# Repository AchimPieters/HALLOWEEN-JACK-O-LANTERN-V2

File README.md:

# HALLOWEEN-JACK-O-LANTERN-V2
 Halloween – Jack O’ Lantern V2: Ultimate Fire Effect

This project is a next-level version of the original [Jack O’ Lantern](#) flickering flame. It uses an ATtiny85 and six individually controlled LEDs to simulate a more realistic and dynamic fire effect — perfect for Halloween decorations, cosplay props, fantasy builds, and magical scenes.

Now with optional *blue flame mode* for a magical, Harry Potter–inspired effect!

---

##  Features

- Powered by ATtiny85 microcontroller  
- 6 individually PWM-controlled LEDs (3× red, 3× yellow)
- Realistic flame flicker with bursts and glow
- Smooth, natural-looking transitions using logarithmic fading
- Optional **Blue Flame Mode** (v2.1.0) using neon blue LED's
- Compact custom PCB included for easy assembly
- Low power – runs on 3×AA batteries

---

##  Bill of Materials

| Qty | Component               |
|-----|-------------------------|
| 1   | ATtiny85 microcontroller |
| 6   | 200Ω resistors           |
| 3   | 3mm Red LED's             |
| 3   | 3mm Yellow LED's          |
| 1   | 3×AA battery holder with switch |
| 3   | AA batteries             |
| 1   | Custom PCB (included in repo) |

Want a magical look? Swap all LED's for **neon blue** versions in firmware v2.1.0.

---

## PCB & Schematic

This repository includes:

- **KiCad project files**
- **Schematic (.sch)**
- **PCB layout (.kicad_pcb)**
- **Gerber files** for manufacturing
- **Render preview** of the assembled board

---

## Circuit Diagram

All LED's are connected to PWM-capable pins on the ATtiny85:  
`PB0–PB5` are used for controlling individual LED's.

> **Note:** `PB5` (pin 1) is the default RESET pin.  
> If you want to use it as output, you'll need to disable RESET via **RSTDISBL fuse**, which requires high voltage programming for future re-flashing.

---

## 3D model

### Regular Setup

### Neonblue Setup

---

## Programming

You can flash the ATtiny85 using any of the following:

- USBasp
- TinyUSB programmer
- Arduino as ISP

Upload the included `.ino` file or compile from source. Programming tools like `avrdude`, `AVRDUDE GUI`, or the Arduino IDE (with core support) will work.

---

## Usage

| Firmware Version | Description                          |
|------------------|--------------------------------------|
| v2.0.0           | Warm flickering with red/yellow LED's|
| v2.1.0           | Cool magical flame with blue LED's   |

- Solder components onto the PCB
- Insert the programmed ATtiny85
- Connect the battery pack and flip the switch

Enjoy your realistic or magical LED fire effect!

---

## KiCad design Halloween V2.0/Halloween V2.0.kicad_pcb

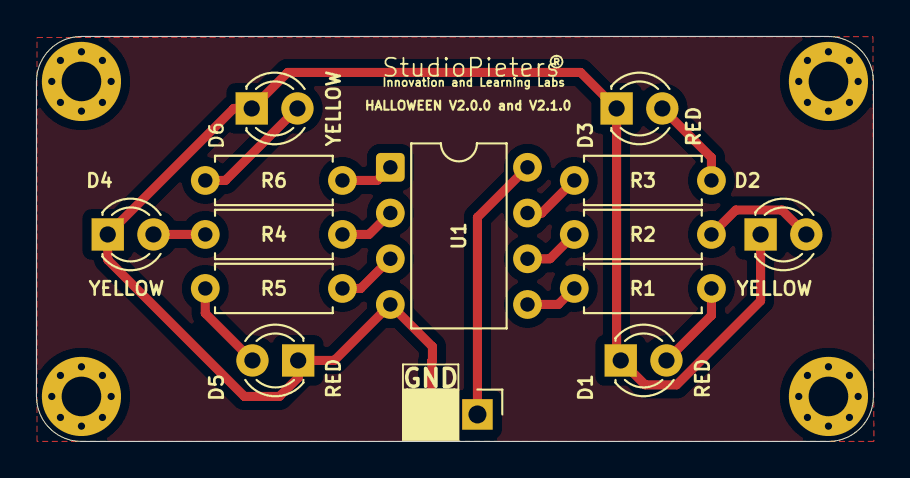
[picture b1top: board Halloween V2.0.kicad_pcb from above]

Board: 2 copper layers, 46.5 x 22.5 mm, 14 parts (0 on the bottom side), 14 nets.

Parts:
BT1: Battery_Box; PinHeader_1x02_P2.54mm_Vertical
D1, D3, D5: RED; LED_D3.0mm
D2, D4, D6: YELLOW; LED_D3.0mm
R1, R2, R3, R4, R5, R6: | 200Ω; R_Axial_DIN0207_L6.3mm_D2.5mm_P7.62mm_Horizontal
U1: ATtiny85-20P; DIP-8_W7.62mm

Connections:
unnamed: BT1.1 (+), U1.8 (VCC)
unnamed: BT1.2 (-), D1.1 (K), D2.1 (K), D3.1 (K), D4.1 (K), D5.1 (K), D6.1 (K), U1.4 (GND)
unnamed: D1.2 (A), R1.2
unnamed: D2.2 (A), R2.2
unnamed: D3.2 (A), R3.2
unnamed: D4.2 (A), R4.2
unnamed: D5.2 (A), R5.2
unnamed: D6.2 (A), R6.2
unnamed: R1.1, U1.5 (AREF/PB0)
unnamed: R2.1, U1.6 (PB1)
unnamed: R3.1, U1.7 (PB2)
unnamed: R4.1, U1.2 (XTAL1/PB3)
unnamed: R5.1, U1.3 (XTAL2/PB4)
unnamed: R6.1, U1.1 (~RESET/PB5)
